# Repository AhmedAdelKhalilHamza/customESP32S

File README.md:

# customESP32S
custom ESP32S board by Eng/ Ahmed Adel

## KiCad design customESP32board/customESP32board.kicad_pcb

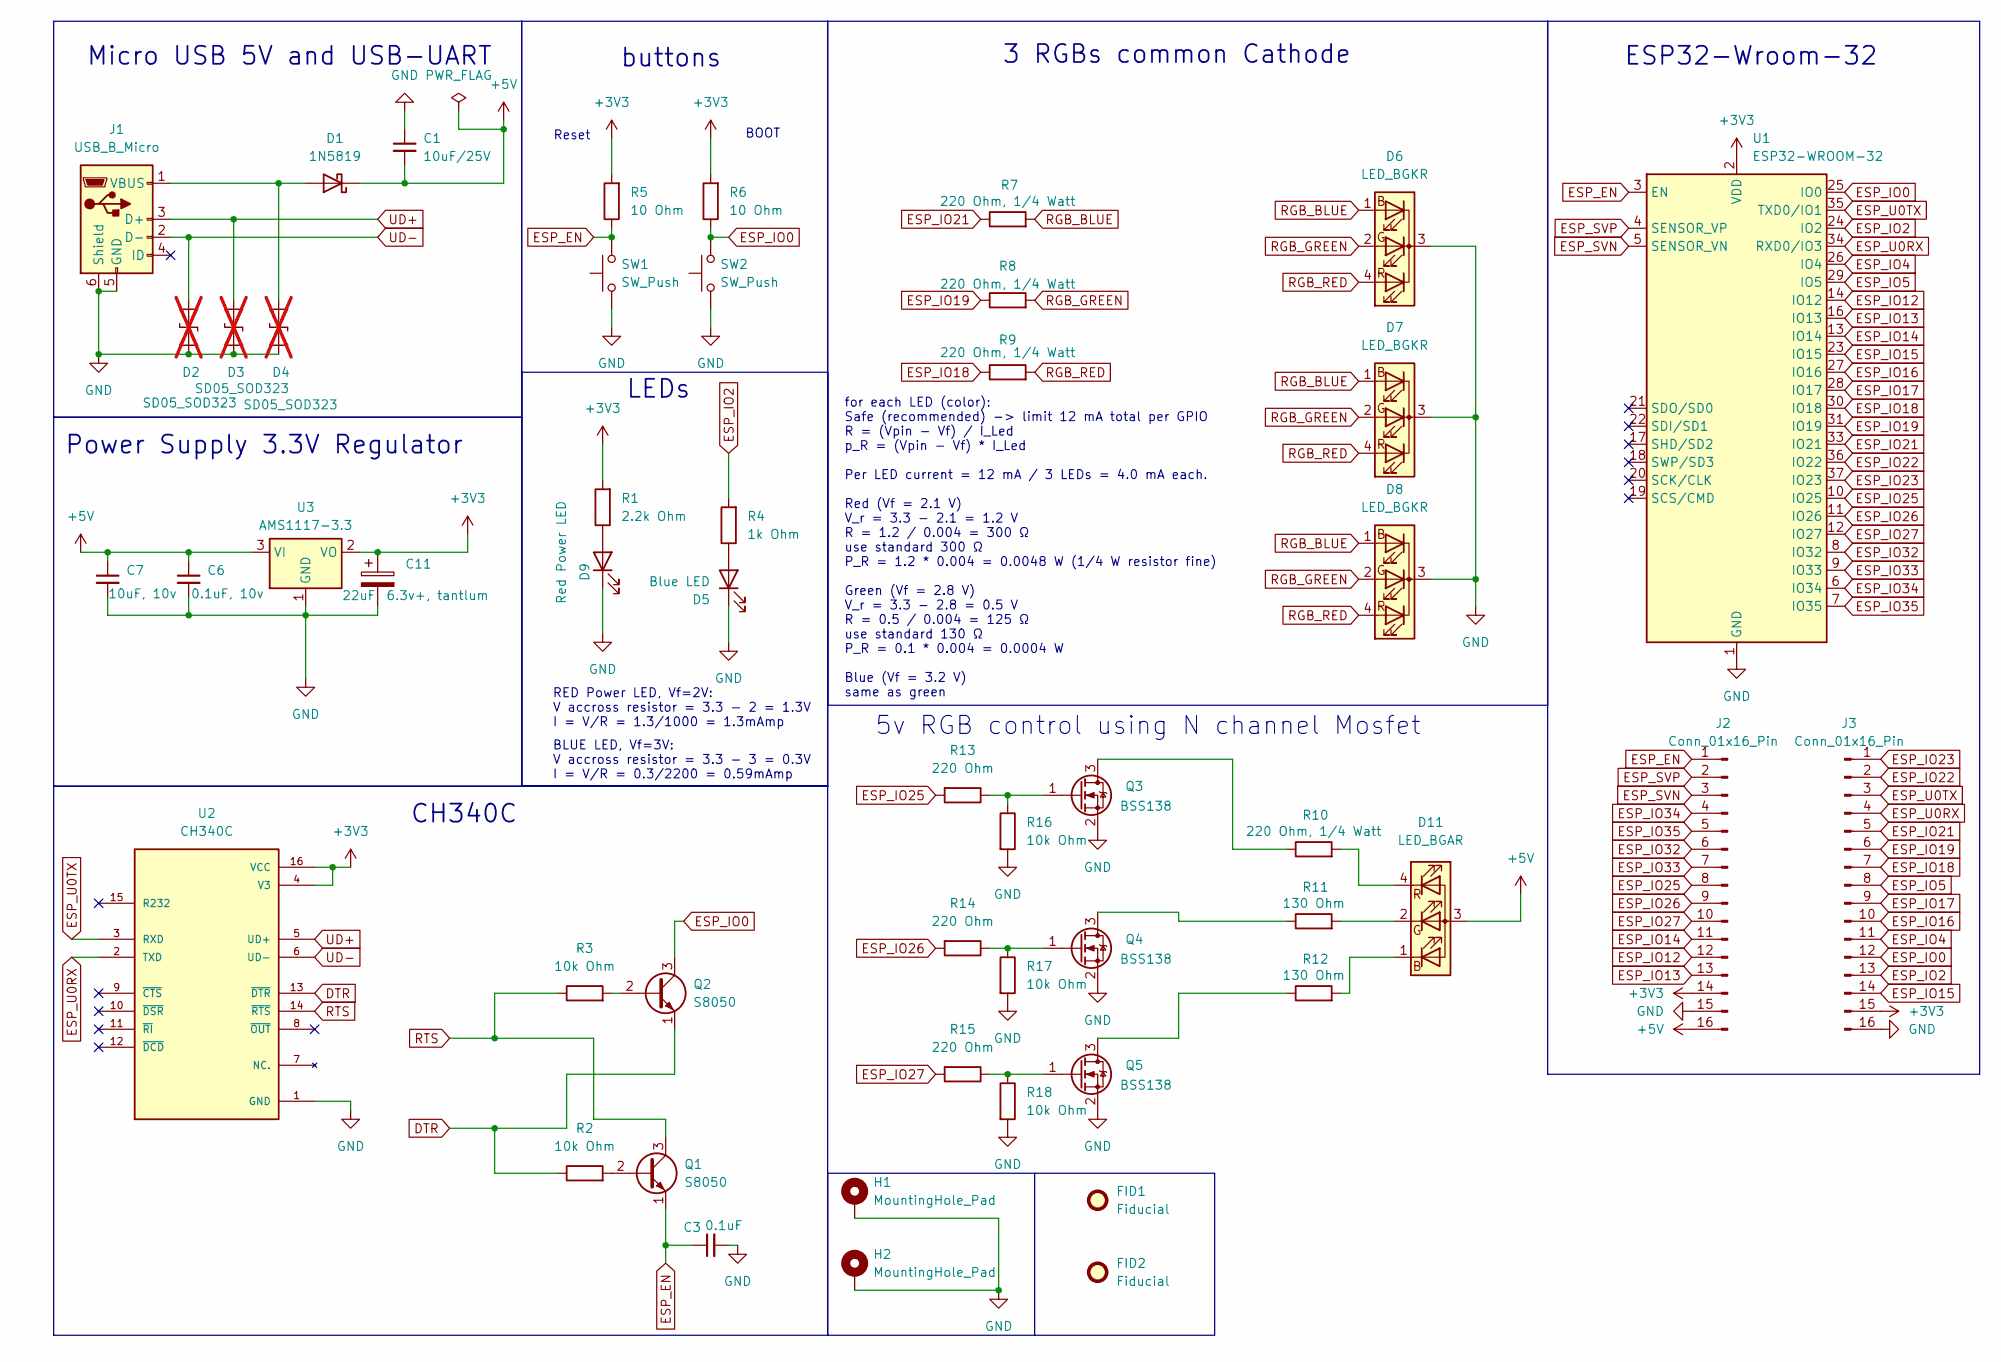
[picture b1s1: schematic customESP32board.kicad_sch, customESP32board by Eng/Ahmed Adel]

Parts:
C1: 10uF/25V; C_0805_2012Metric
C3: 0.1uF; C_0603_1608Metric
C6: 0.1uF, 10v; C_0603_1608Metric
C7: 10uF, 10v; C_0805_2012Metric
C11: 22uF, 6.3v+, tantlum; C_1206_3216Metric
D1: 1N5819; D_SMA_Handsoldering
D2, D3, D4: SD05_SOD323; D_SOD-323; not fitted
D5: Blue LED; LED_0603_1608Metric
D6, D7, D8: LED_BGKR; LED_D5.0mm-4_RGB
D9: Red Power LED; LED_0603_1608Metric
D11: LED_BGAR; LED_D5.0mm-4_RGB
FID1, FID2: Fiducial; Fiducial_0.5mm_Mask1.5mm
H1, H2: MountingHole_Pad; MountingHole_2.2mm_M2_Pad_Via
J1: USB_B_Micro; USB_Micro-B_Wuerth_629105150521
J2, J3: Conn_01x16_Pin; PinHeader_1x16_P2.54mm_Vertical
Q1, Q2: S8050; SOT-23
Q3, Q4, Q5: BSS138; SOT-23
R1: 2.2k Ohm; R_0805_2012Metric
R2, R3, R16, R17, R18: 10k Ohm; R_0805_2012Metric
R4: 1k Ohm; R_0603_1608Metric
R5, R6: 10 Ohm; R_1206_3216Metric
R7, R8, R9, R10: 220 Ohm, 1/4 Watt; R_0603_1608Metric
R11, R12: 130 Ohm; R_0805_2012Metric
R13, R14, R15: 220 Ohm; R_0603_1608Metric
SW1, SW2: SW_Push; SW_TS-1088-AR02016
U1: ESP32-WROOM-32
U2: CH340C; PARTREV 2G
U3: AMS1117-3.3; SOT-223-3_TabPin2

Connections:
+3V3: C11.1, J2.14, J3.15, R1.2, R5.2, R6.2, U1.2 (VDD), U2.4 (V3), U2.16 (VCC), U3.2 (VO)
+5V: C1.2, C6.1, C7.1, D1.1 (K), D11.3 (A), J2.16, U3.3 (VI)
DTR: Q2.1 (E), R2.1, U2.13 (~DTR)
ESP_EN: C3.1, J2.1, Q1.1 (E), R5.1, SW1.2, U1.3 (EN)
ESP_IO0: J3.12, Q2.3 (C), R6.1, SW2.2, U1.25 (IO0)
ESP_IO2: J3.13, R4.2, U1.24 (IO2)
ESP_IO4: J3.11, U1.26 (IO4)
ESP_IO5: J3.8, U1.29 (IO5)
ESP_IO12: J2.12, U1.14 (IO12)
ESP_IO13: J2.13, U1.16 (IO13)
ESP_IO14: J2.11, U1.13 (IO14)
ESP_IO15: J3.14, U1.23 (IO15)
ESP_IO16: J3.10, U1.27 (IO16)
ESP_IO17: J3.9, U1.28 (IO17)
ESP_IO18: J3.7, R9.1, U1.30 (IO18)
ESP_IO19: J3.6, R8.1, U1.31 (IO19)
ESP_IO21: J3.5, R7.1, U1.33 (IO21)
ESP_IO22: J3.2, U1.36 (IO22)
ESP_IO23: J3.1, U1.37 (IO23)
ESP_IO25: J2.8, R13.2, U1.10 (IO25)
ESP_IO26: J2.9, R14.2, U1.11 (IO26)
ESP_IO27: J2.10, R15.2, U1.12 (IO27)
ESP_IO32: J2.6, U1.8 (IO32)
ESP_IO33: J2.7, U1.9 (IO33)
ESP_IO34: J2.4, U1.6 (IO34)
ESP_IO35: J2.5, U1.7 (IO35)
ESP_SVN: J2.3, U1.5 (SENSOR_VN)
ESP_SVP: J2.2, U1.4 (SENSOR_VP)
ESP_U0RX: J3.4, U1.34 (RXD0/IO3), U2.2 (TXD)
ESP_U0TX: J3.3, U1.35 (TXD0/IO1), U2.3 (RXD)
GND: C1.1, C3.2, C6.2, C7.2, C11.2, D2.1 (A1), D3.1 (A1), D4.1 (A1), D5.1 (K), D6.3 (K), D7.3 (K), D8.3 (K), D9.1 (K), H1.1, H2.1, J1.5 (GND), J1.6 (Shield), J2.15, J3.16, Q3.2 (S), Q4.2 (S), Q5.2 (S), R16.2, R17.2, R18.2, SW1.1, SW2.1, U1.1 (GND), U1.15 (GND), U1.38 (GND), U1.39 (GND), U2.1 (GND), U3.1 (GND)
unnamed: D1.2 (A), D4.2 (A2), J1.1 (VBUS)
unnamed: D5.2 (A), R4.1
unnamed: D9.2 (A), R1.1
unnamed: D11.1 (BK), R12.2
unnamed: D11.2 (GK), R11.2
unnamed: D11.4 (RK), R10.2
unnamed: Q1.2 (B), R2.2
unnamed: Q2.2 (B), R3.2
unnamed: Q3.3 (D), R10.1
unnamed: Q3.1 (G), R13.1, R16.1
unnamed: Q4.3 (D), R11.1
unnamed: Q4.1 (G), R14.1, R17.1
unnamed: Q5.3 (D), R12.1
unnamed: Q5.1 (G), R15.1, R18.1
RGB_BLUE: D6.1 (BA), D7.1 (BA), D8.1 (BA), R7.2
RGB_GREEN: D6.2 (GA), D7.2 (GA), D8.2 (GA), R8.2
RGB_RED: D6.4 (RA), D7.4 (RA), D8.4 (RA), R9.2
RTS: Q1.3 (C), R3.1, U2.14 (~RTS)
UD+: D3.2 (A2), J1.3 (D+), U2.5 (UD+)
UD-: D2.2 (A2), J1.2 (D-), U2.6 (UD-)

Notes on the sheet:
3 RGBs common Cathode
buttons
BOOT
Power Supply 3.3V Regulator
LEDs
ESP32-Wroom-32
Reset
for each LED (color): Safe (recommended) -> limit 12 mA total per GPIO R = (Vpin - Vf) / I_Led p_R = (Vpin - Vf) * I_Led Per LED current = 12 mA / 3 LEDs = 4.0 mA each. Red (Vf = 2.1 V) V_r = 3.3 − 2.1 = 1.2 V R = 1.2 / 0.004 = 300 Ω use standard 300 Ω P_R = 1.2 * 0.004 = 0.0048 W (1/4 W resistor f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
BLUE LED, Vf=3V: V accross resistor = 3.3 - 3 = 0.3V I = V/R = 0.3/2200 = 0.59mAmp
5v RGB control using N channel Mosfet
Micro USB 5V and USB-UART
CH340C
RED Power LED, Vf=2V: V accross resistor = 3.3 - 2 = 1.3V I = V/R = 1.3/1000 = 1.3mAmp

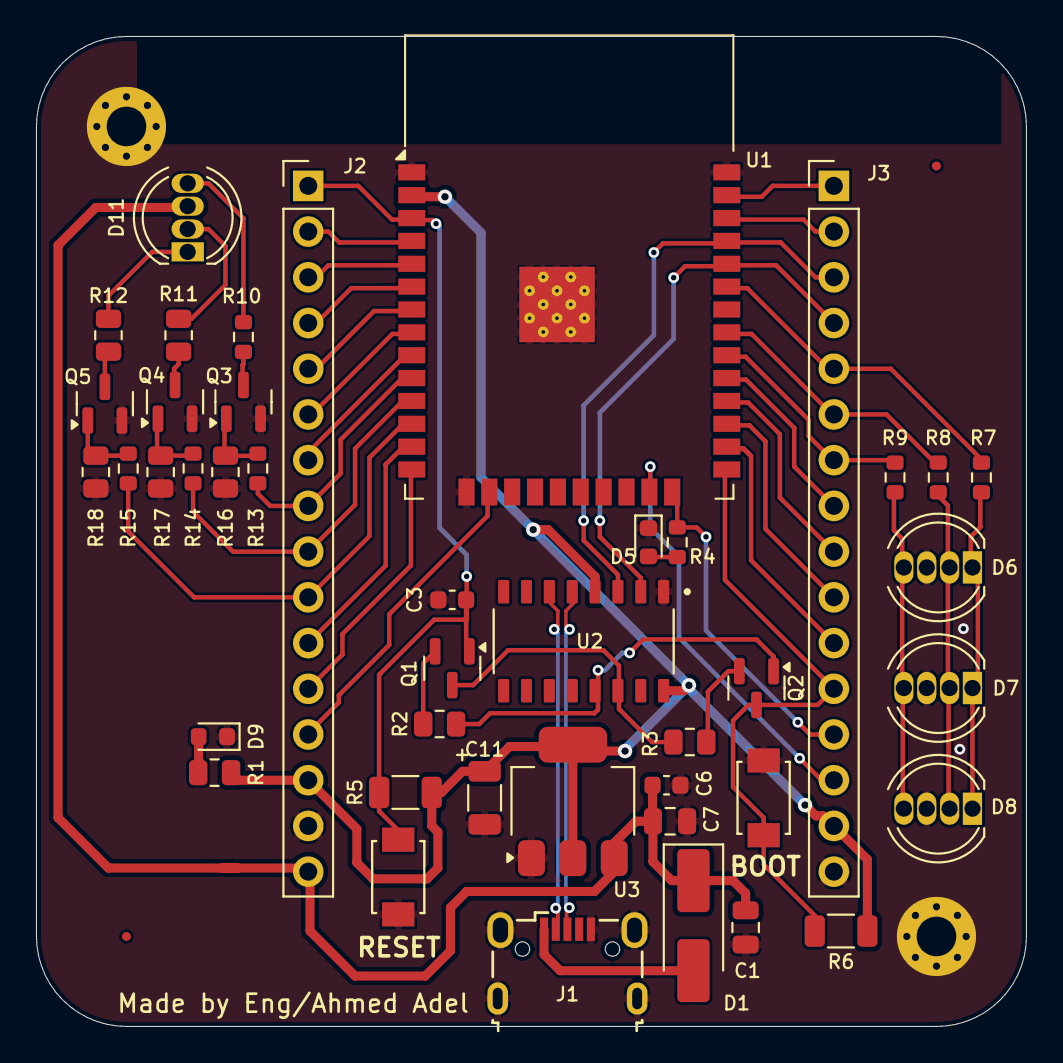
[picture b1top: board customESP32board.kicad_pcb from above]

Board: 2 copper layers, 55.0 x 55.0 mm, 47 parts (0 on the bottom side), 51 nets.

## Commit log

2025-09-23 intial Commit
    prepared files for KiCAD
2025-09-23 upload reference scchematic and create library for custom components
2025-09-23 finished two USB micro connections with their protection circuit
2025-09-24 added AMS1117-3.3v LDO schematic design
2025-09-26 updated schematic to match ESP32-WROOM-V2 dev board instaed of ESP32-S3 dev board
2025-09-26 finalized esp32 board schematic
2025-09-26 calculated LEDs current limiting resistance for power and test led D9 and D5
2025-09-27 added RGB controlled by esp32 pins using N channel MOSFET bss138
2025-09-27 assigned CH340C footprint library
2025-09-27 assigned footprint to all symbols
2025-09-27 removed RT9161A CAD model
2025-09-27 generated BOM and created layout file
2025-09-27 continued layout, removed tvs diodes
2025-09-27 continued layout
2025-09-29 finished routing
2025-09-29 re-routing
2025-09-29 updated routing
2025-09-30 adjusted placement to 0.1 mm grid
2025-10-01 finalized board routing, generated gerbers and drill files also generated step file
2025-10-01 step file generation
2025-10-01 updated rgb led 3d model orientation
2025-10-01 updated rendered 3d images
2025-10-11 updated placement for metanoio pcb production rules
2025-10-11 updates check
